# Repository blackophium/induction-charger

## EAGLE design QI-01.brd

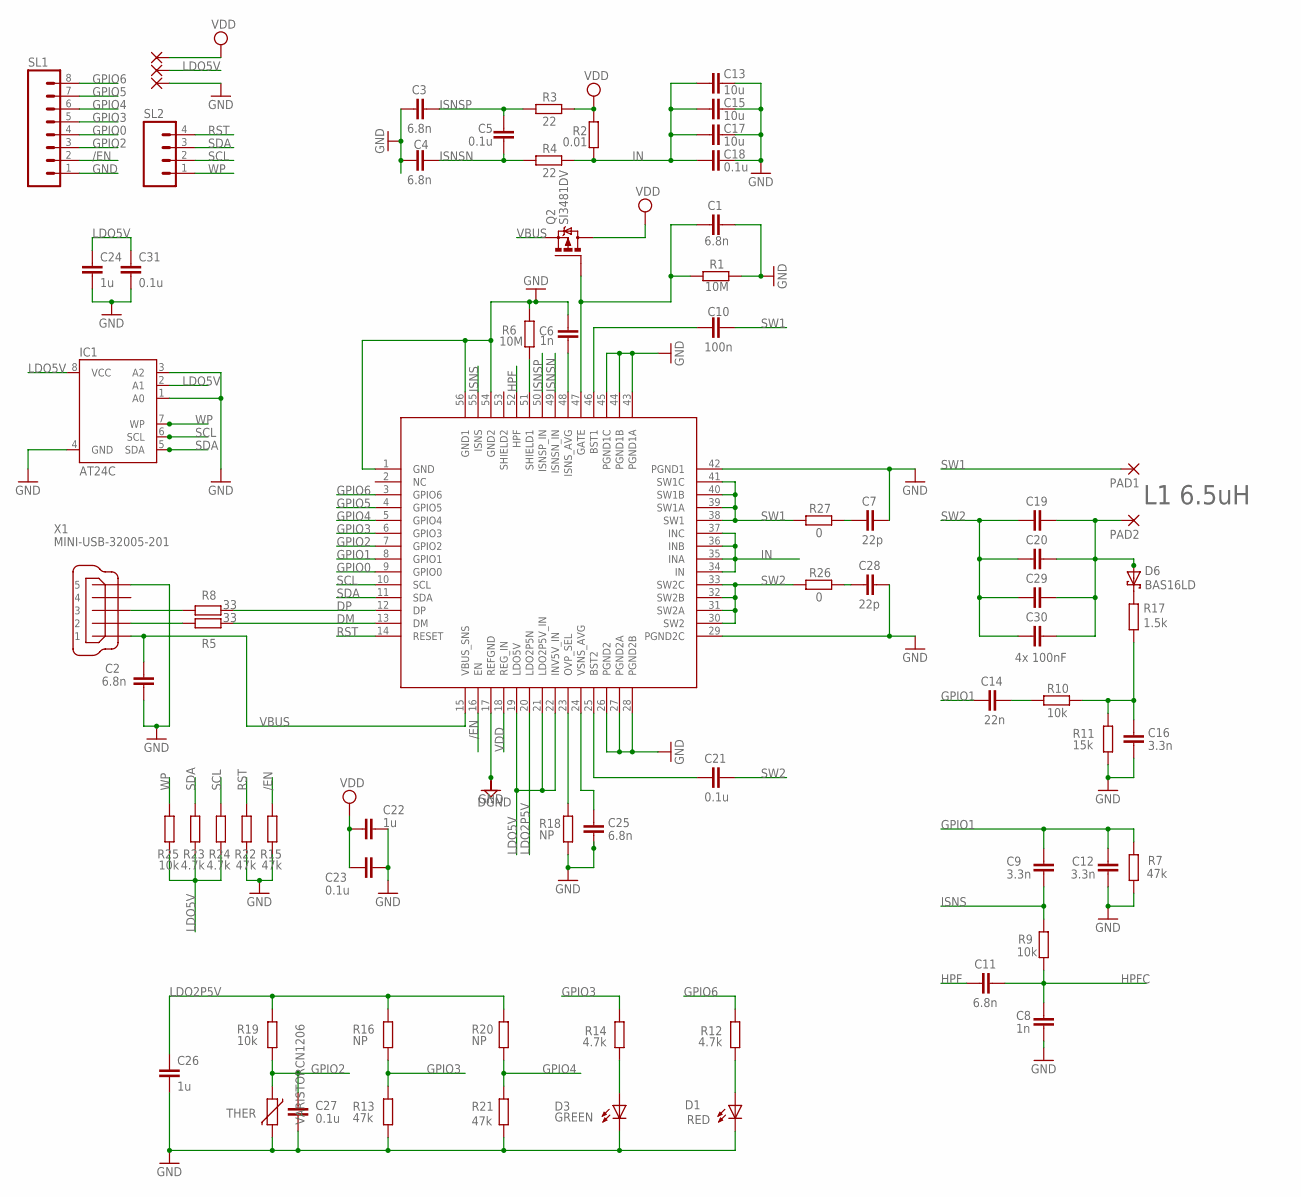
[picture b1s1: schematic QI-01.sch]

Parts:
C1, C2, C3, C4, C11, C25: 6.8n; C0402
C5, C18, C21, C23, C27, C31: 0.1u; C0402
C6, C8: 1n; C0402
C7, C28: 22p; C0402
C9, C12, C16: 3.3n; C0402
C10: 100n; C0402
C13, C15, C17: 10u; C0805
C14: 22n; C0402
C19, C20, C29, C30: 100n; C1206
C22, C24, C26: 1u; C0402
D1: RED; SML0603
D3: GREEN; SML0603
D6: BAS16LD; SMB
IC1: AT24C; TSSOP8
PAD1, PAD2: 2,54/1,0
PAD3, PAD4, PAD5: 2,15/1,0
Q2: SI3481DV; TSOP-6.PAC
R1, R6: 10M; R0402
R2: 0.01; R0805
R3, R4: 22; R0402
R5, R8: 33; R0402
R7: 47k; R0402
R9, R10, R19, R25: 10k; R0402
R11: 15k; R0402
R12, R14, R23, R24: 4.7k; R0402
R13, R15, R21, R22: 47k; R0603
R16, R18, R20: NP; R0402
R17: 1.5k; R0402
R26, R27: 0; R0402
SL1: M08; 08P
SL2: M04; 04P
THER: VARISTORCN1206; CT/CN1206
U$1: VFQFPN; ZADANIE
X1: MINI-USB-32005-201; 32005-201

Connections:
/EN: R15.2, SL1.2, U$1.16 (EN)
DM: R5.2, U$1.13 (DM)
DP: R8.2, U$1.12 (DP)
GND: C1.1, C2.1, C3.1, C4.1, C6.1, C7.1, C8.1, C12.1, C13.1, C15.1, C16.2, C17.1, C18.1, C22.1, C23.1, C24.2, C25.2, C26.2, C27.2, C28.1, C31.2, D1.C, D3.C, IC1.1 (A0), IC1.3 (A2), IC1.4 (GND), PAD5.1, R1.2, R6.2, R7.1, R11.1, R13.1, R15.1, R18.1, R21.1, R22.1, SL1.1, THER.2, U$1.1 (GND), U$1.17 (REFGND), U$1.26 (PGND2), U$1.27 (PGND2A), U$1.28 (PGND2B), U$1.29 (PGND2C), U$1.42 (PGND1), U$1.43 (PGND1A), U$1.44 (PGND1B), U$1.45 (PGND1C), U$1.54 (GND2), U$1.56 (GND1), X1.5
GPIO0: SL1.4, U$1.9 (GPIO0)
GPIO1: C9.2, C12.2, C14.1, R7.2, U$1.8 (GPIO1)
GPIO2: C27.1, R19.1, SL1.3, THER.1, U$1.7 (GPIO2)
GPIO3: R13.2, R14.2, R16.1, SL1.5, U$1.6 (GPIO3)
GPIO4: R20.1, R21.2, SL1.6, U$1.5 (GPIO4)
GPIO5: SL1.7, U$1.4 (GPIO5)
GPIO6: R12.2, SL1.8, U$1.3 (GPIO6)
HPF: C11.1, U$1.52 (HPF)
HPFC: C8.2, C11.2, R9.1
IN: C13.2, C15.2, C17.2, C18.2, R2.1, R4.2, U$1.34 (IN), U$1.35 (INA), U$1.36 (INB), U$1.37 (INC)
ISNS: C9.1, R9.2, U$1.55 (ISNS)
ISNSN: C4.2, C5.1, R4.1, U$1.49 (ISNSN_IN)
ISNSP: C3.2, C5.2, R3.1, U$1.50 (ISNSP_IN)
LDO2P5V: C26.1, R16.2, R19.2, R20.2, U$1.20 (LDO2P5N)
LDO5V: C24.1, C31.1, IC1.2 (A1), IC1.8 (VCC), PAD4.1, R23.1, R24.1, R25.1, U$1.19 (LDO5V), U$1.21 (LDO2P5V_IN), U$1.22 (INV5V_IN)
unnamed: C10.2, U$1.46 (BST1)
unnamed: R18.2, U$1.23 (OVP_SEL)
unnamed: C7.2, R27.2
unnamed: C16.1, R10.1, R11.2, R17.1
unnamed: C21.2, U$1.25 (BST2)
unnamed: C14.2, R10.2
unnamed: C25.1, U$1.24 (VSNS_AVG)
unnamed: R8.1, X1.3
unnamed: R5.1, X1.2
unnamed: C19.1, C20.1, C29.1, C30.1, D6.A, PAD2.1
unnamed: D6.C, R17.2
unnamed: C28.2, R26.2
unnamed: C6.2, U$1.48 (ISNS_AVG)
unnamed: C1.2, Q2.3 (G), R1.1, U$1.47 (GATE)
unnamed: R6.1, U$1.51 (SHIELD1)
unnamed: D3.A, R14.1
unnamed: D1.A, R12.1
RST: R22.2, SL2.4, U$1.14 (RESET)
SCL: IC1.6 (SCL), R24.2, SL2.2, U$1.10 (SCL)
SDA: IC1.5 (SDA), R23.2, SL2.3, U$1.11 (SDA)
SW1: C10.1, PAD1.1, R27.1, U$1.38 (SW1), U$1.39 (SW1A), U$1.40 (SW1B), U$1.41 (SW1C)
SW2: C19.2, C20.2, C21.1, C29.2, C30.2, R26.1, U$1.30 (SW2), U$1.31 (SW2A), U$1.32 (SW2B), U$1.33 (SW2C)
VBUS: C2.2, Q2.4 (S), U$1.15 (VBUS_SNS), X1.1
VDD: C22.2, C23.2, PAD3.1, Q2.1 (D), Q2.2 (D), Q2.5 (D), Q2.6 (D), R2.2, R3.2, U$1.18 (REG_IN)
WP: IC1.7 (WP), R25.2, SL2.1

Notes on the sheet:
L1 6.5uH
4x 100nF

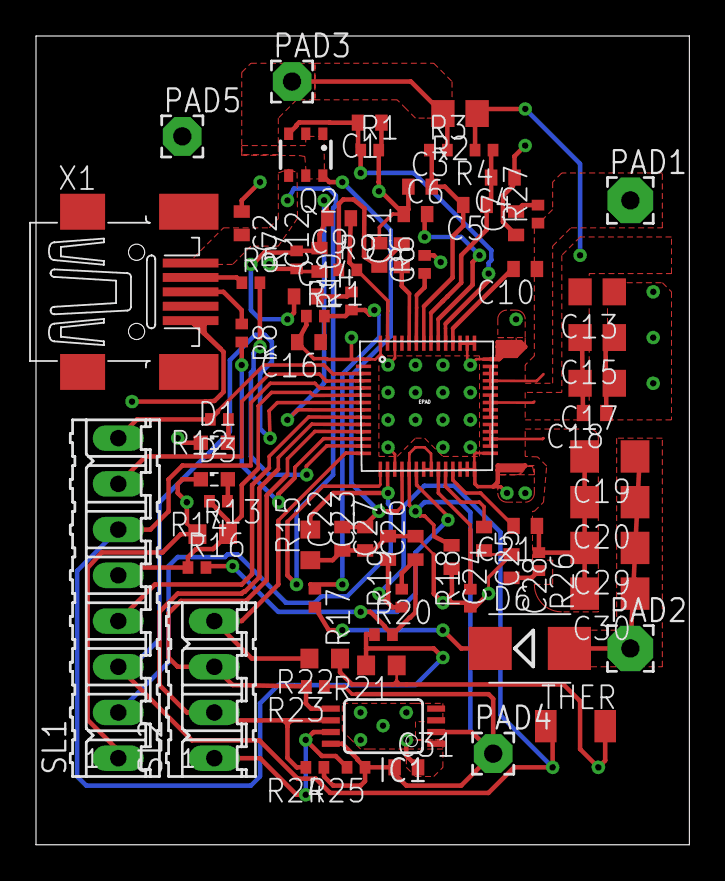
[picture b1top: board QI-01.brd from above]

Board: 2 copper layers, 36.3 x 44.9 mm, 73 parts (0 on the bottom side), 44 nets.
